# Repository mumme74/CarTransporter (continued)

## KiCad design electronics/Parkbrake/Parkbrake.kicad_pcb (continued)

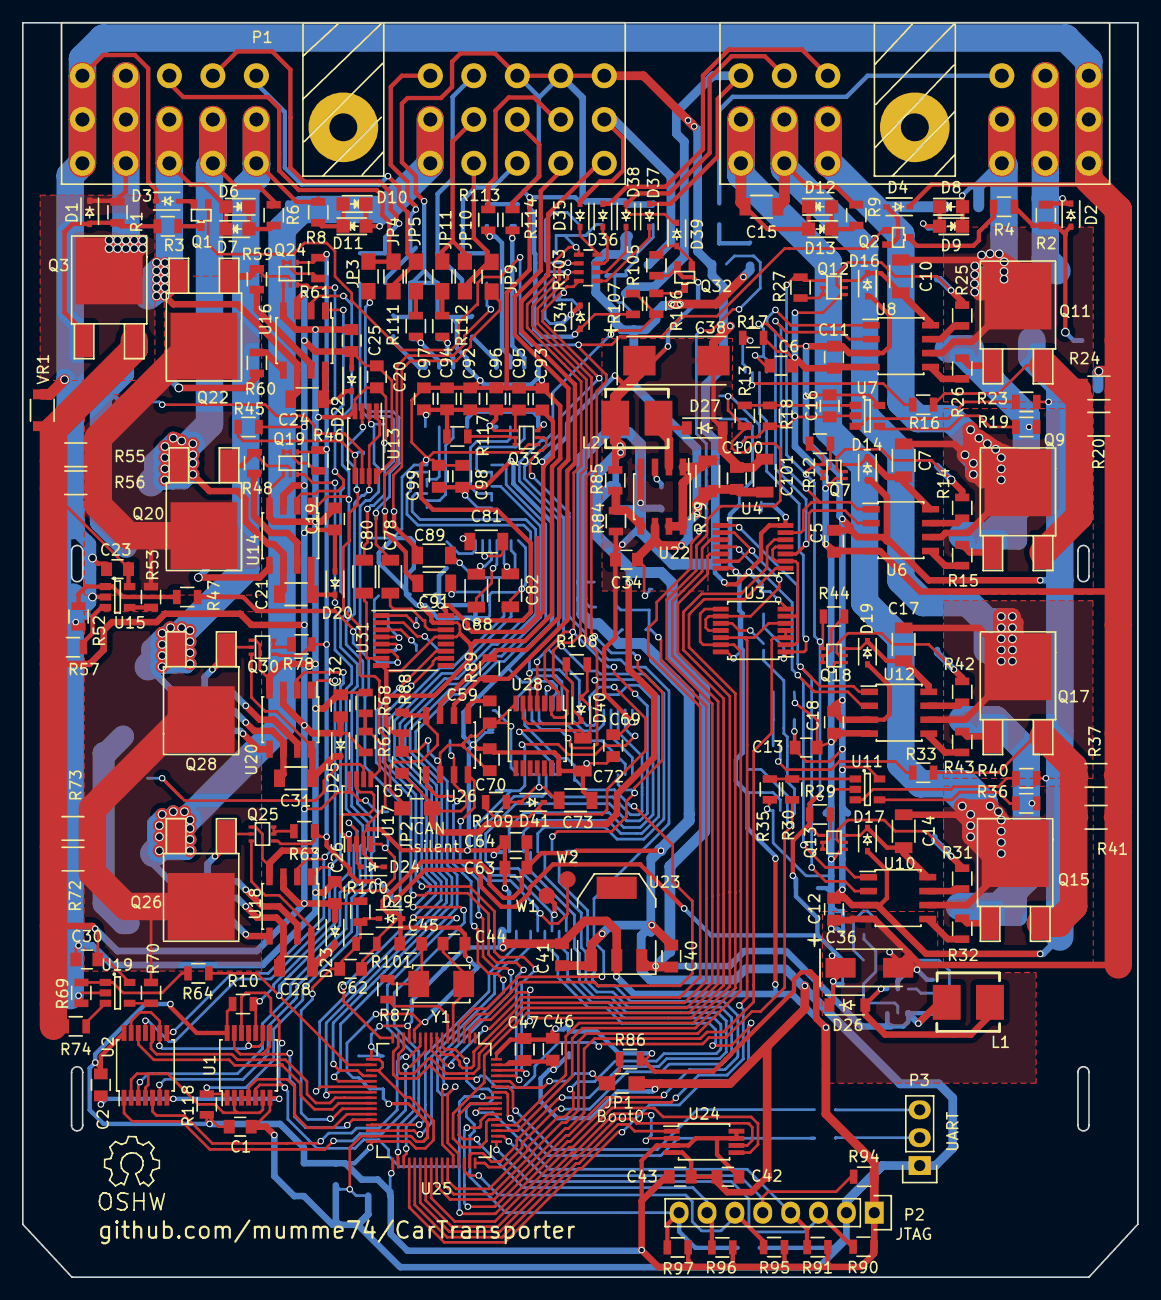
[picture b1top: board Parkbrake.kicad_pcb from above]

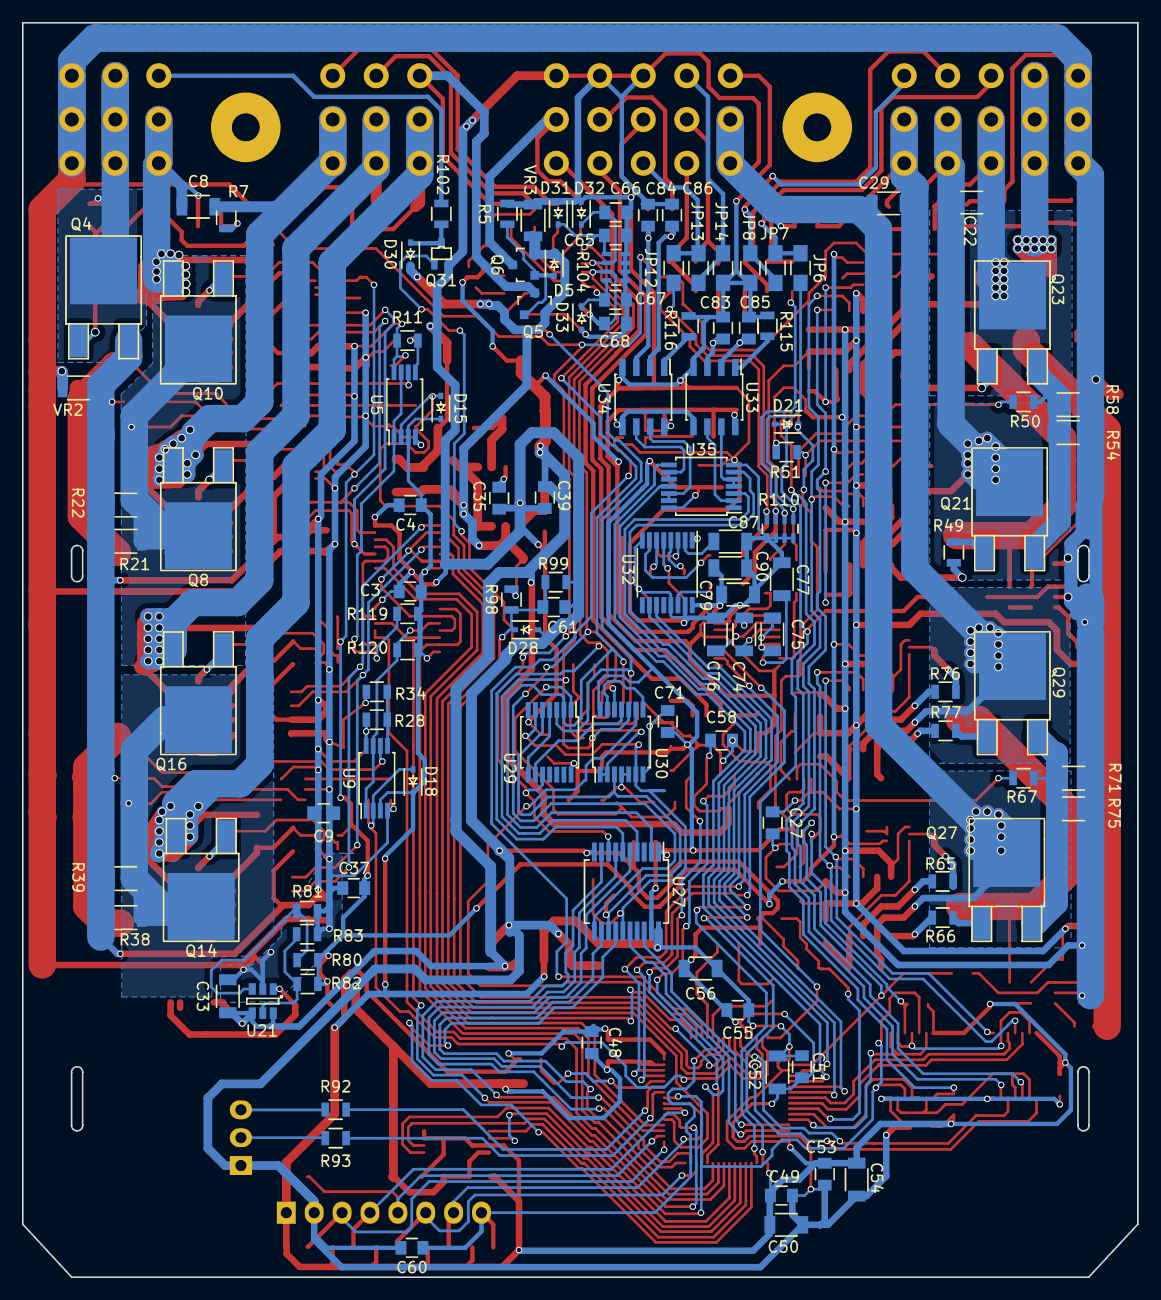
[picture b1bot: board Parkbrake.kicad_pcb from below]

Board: 2 copper layers, 101.6 x 114.3 mm, 355 parts (114 on the bottom side), 260 nets.

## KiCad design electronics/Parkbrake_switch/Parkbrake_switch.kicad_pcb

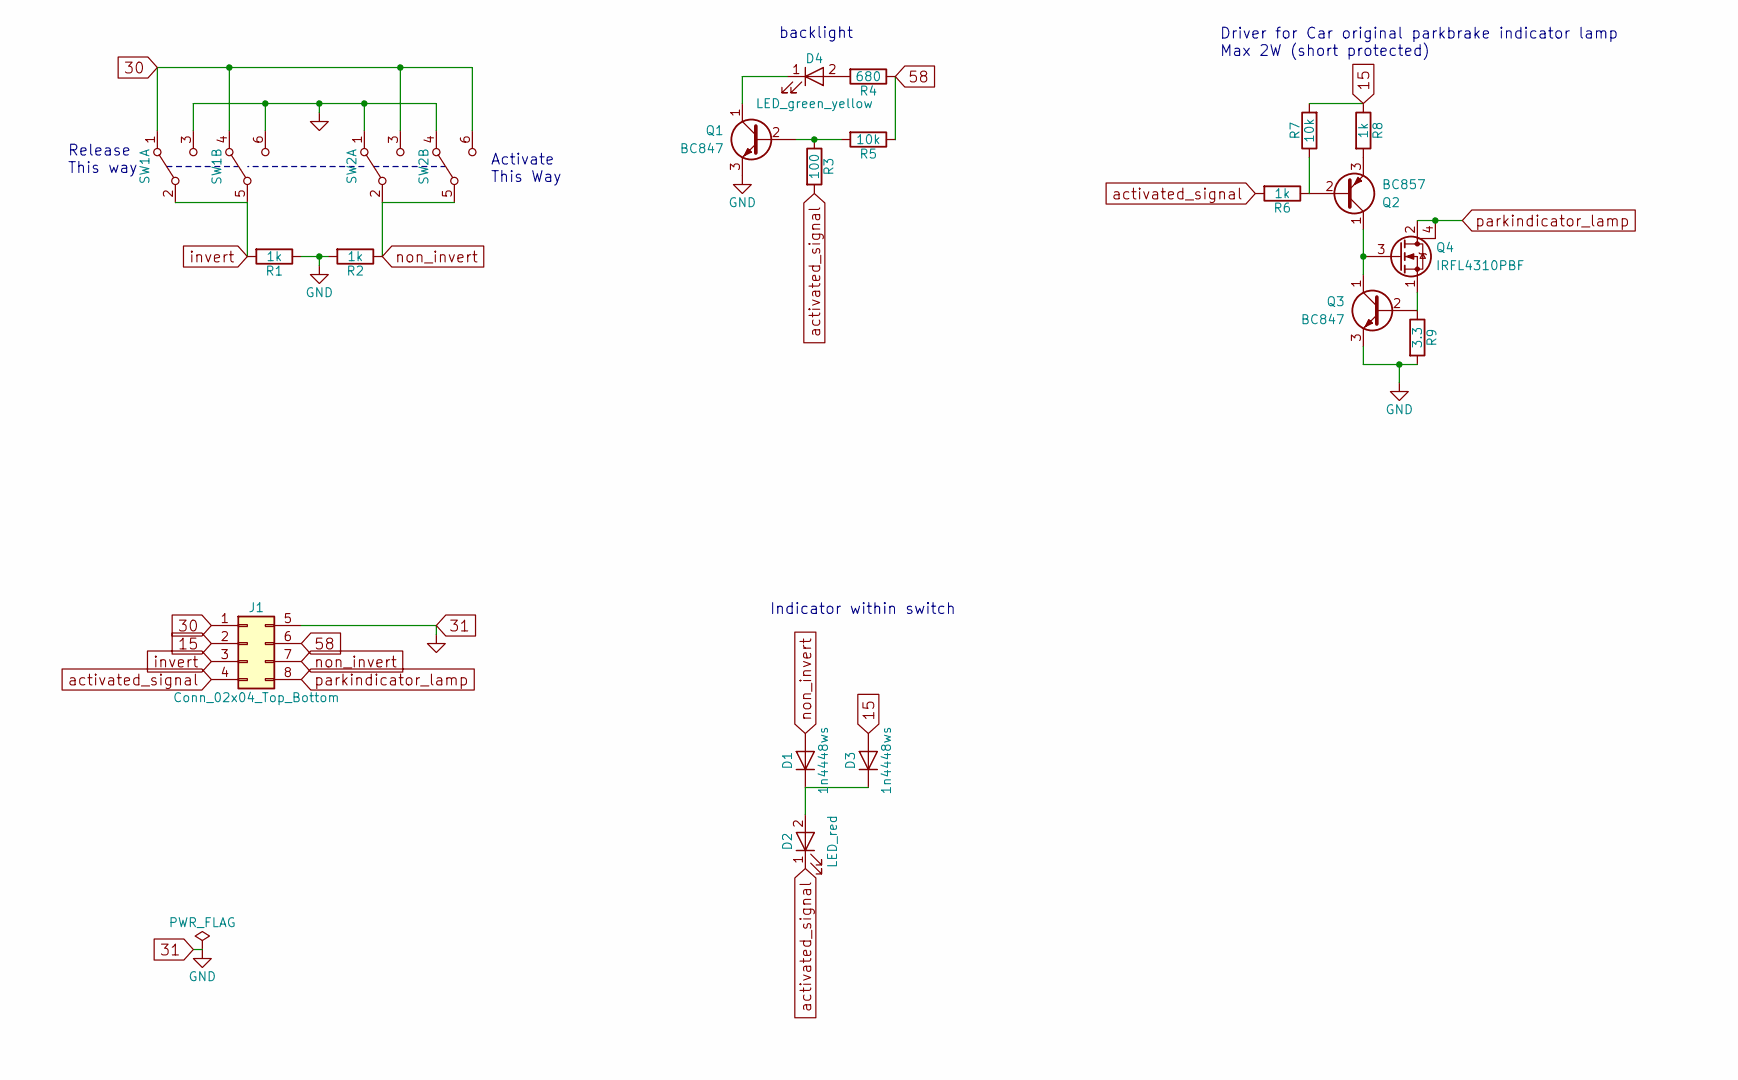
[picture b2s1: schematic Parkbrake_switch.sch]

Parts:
D1, D3: 1n4448ws; SOD-323; farnell 2453724
D2: LED_red; LED_0603; farnell 2687488
D4: LED_green_yellow; LED_0603; farnell 2762558
J1: Conn_02x04_Top_Bottom; Pin_Header_Straight_2x04_Pitch2.54mm; farnell 2356133
Q1, Q3: BC847; SOT-23; farnell 1574344
Q2: BC857; SOT-23; farnell 1773640
Q4: IRFL4310PBF; SOT-223; farnell 2101414
R1, R2, R6, R8: 1k; R_0805; farnell 2447587
R3: 100; R_0805; farnell 2694094
R4: 680; R_0805; farnell 1653028
R5, R7: 10k; R_0805; farnell 2446870
R9: 3.3; R_0805; farnell 2447656
SW1, SW2: SW_DPDT_x2; SPPH410100; farnell 1435768

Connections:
15: D3.2 (A), J1.2, R7.2, R8.1
30: J1.1, SW1.1 (A), SW1.4 (A), SW2.3 (C), SW2.6 (C)
31: J1.5, Q1.3 (E), Q3.3 (E), R1.1, R2.2, R9.2, SW1.3 (C), SW1.6 (C), SW2.1 (A), SW2.4 (A)
58: J1.6, R4.1, R5.1
unnamed: D1.1 (K), D2.2 (A), D3.1 (K)
unnamed: D4.1 (K), Q1.1 (C)
unnamed: D4.2 (A), R4.2
unnamed: Q1.2 (B), R3.1, R5.2
unnamed: Q2.1 (C), Q3.1 (C), Q4.3 (G)
unnamed: Q2.2 (B), R6.1, R7.1
unnamed: Q2.3 (E), R8.2
unnamed: Q3.2 (B), Q4.1 (S), R9.1
activated_signal: D2.1 (K), J1.4, R3.2, R6.2
invert: J1.3, R1.2, SW1.2 (B), SW1.5 (B)
non_invert: D1.2 (A), J1.7, R2.1, SW2.2 (B), SW2.5 (B)
parkindicator_lamp: J1.8, Q4.2 (D), Q4.4 (D)

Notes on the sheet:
backlight
Driver for Car original parkbrake indicator lamp Max 2W (short protected)
Indicator within switch
Release This way
Activate This Way

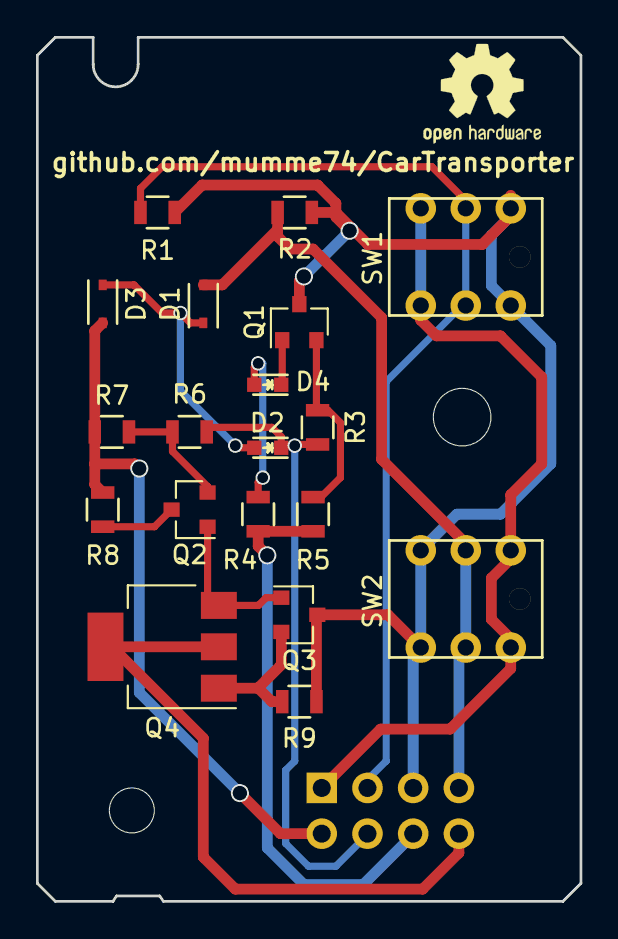
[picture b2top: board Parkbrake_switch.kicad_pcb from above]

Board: 2 copper layers, 30.2 x 48.0 mm, 20 parts (1 on the bottom side), 16 nets.

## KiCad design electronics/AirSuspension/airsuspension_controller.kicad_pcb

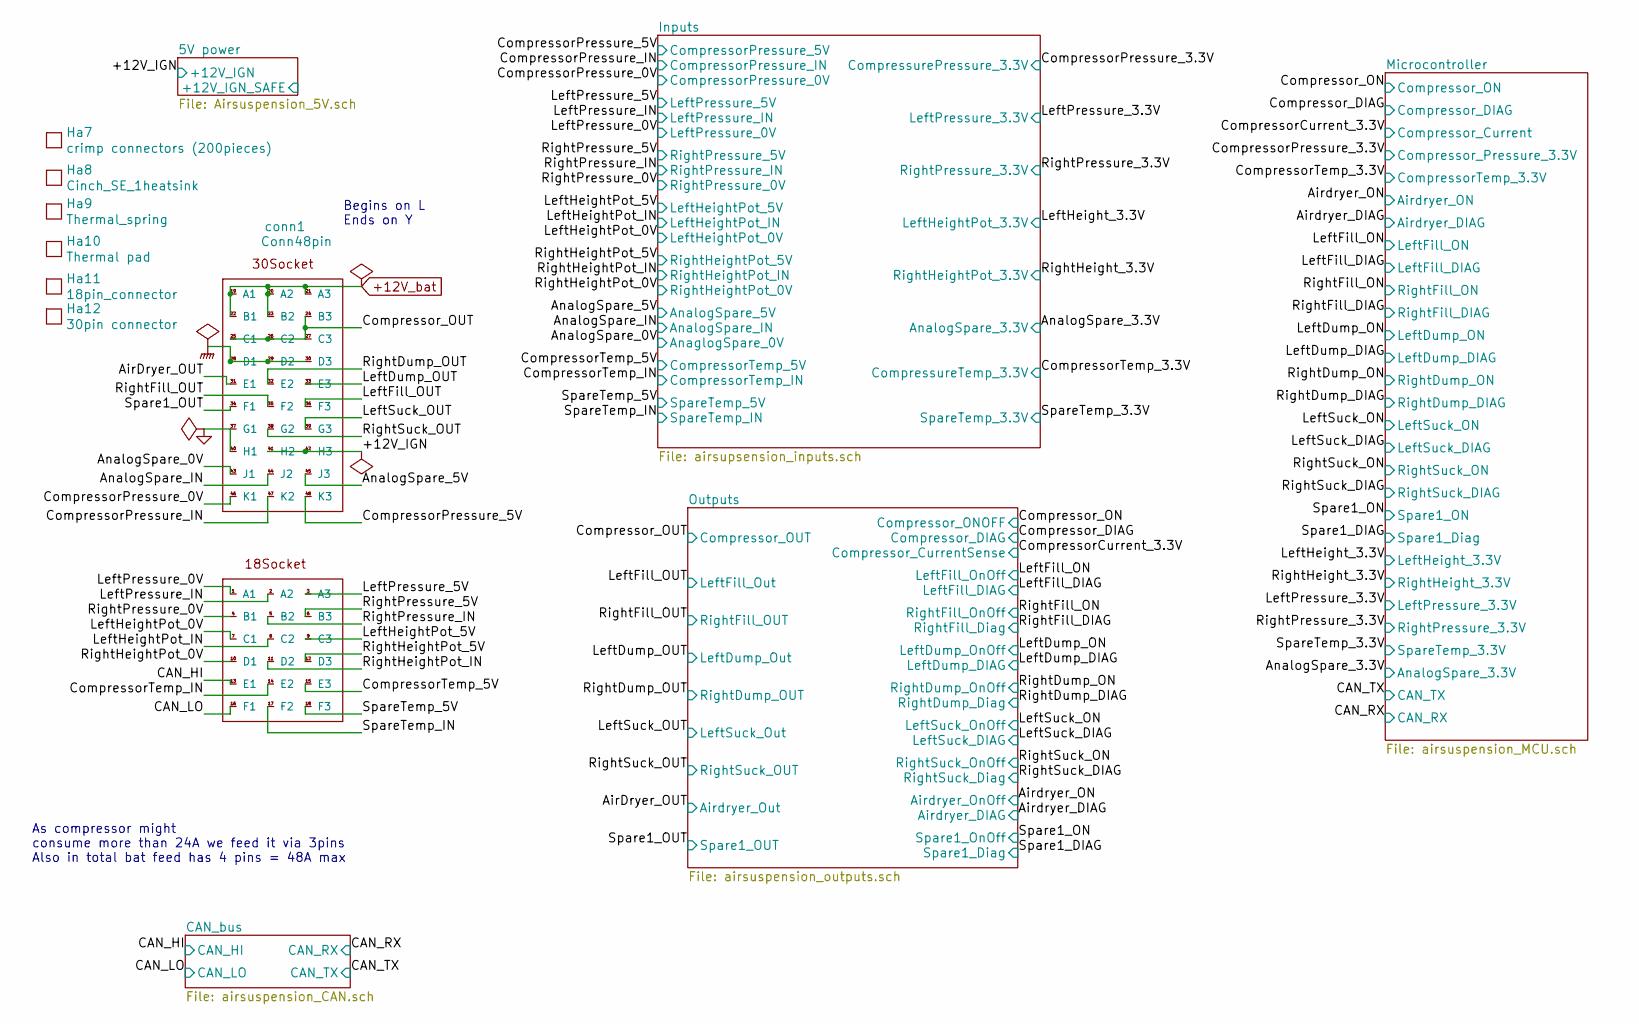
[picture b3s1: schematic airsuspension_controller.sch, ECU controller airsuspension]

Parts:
Ha7: crimp connectors (200pieces); part 4250000873; farnell 1282210
Ha8: Cinch_SE_1heatsink; part 5810130042; farnell 1282197
Ha9: Thermal_spring; part 5810000021; farnell 1282203
Ha10: Thermal pad; part FCTS73-05N; farnell 2289473
Ha11: 18pin_connector; part 5810118023; farnell 1282205
Ha12: 30pin connector; part 5810130028; farnell 1282206
conn1: Conn48pin; part 5810148007; farnell 1282184

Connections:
+12V_bat: conn1.19 (A1), conn1.20 (A2), conn1.21 (A3), conn1.22 (B1), conn1.23 (B2); also elsewhere on the board
/+12V_IGN: conn1.41 (H2), conn1.42 (H3); also elsewhere on the board
/AirDryer_OUT: conn1.31 (E1); also elsewhere on the board
/AnalogSpare_5V: conn1.45 (J3); also elsewhere on the board
/AnalogSpare_IN: conn1.44 (J2); also elsewhere on the board
/CAN_HI: conn1.13 (E1); also elsewhere on the board
/CAN_LO: conn1.16 (F1); also elsewhere on the board
/CompressorPressure_5V: conn1.48 (K3); also elsewhere on the board
/CompressorPressure_IN: conn1.47 (K2); also elsewhere on the board
/CompressorTemp_5V: conn1.15 (E3); also elsewhere on the board
/CompressorTemp_IN: conn1.14 (E2); also elsewhere on the board
/Compressor_OUT: conn1.24 (B3), conn1.25 (C1), conn1.26 (C2), conn1.27 (C3); also elsewhere on the board
/LeftDump_OUT: conn1.33 (E3); also elsewhere on the board
/LeftFill_OUT: conn1.36 (F3); also elsewhere on the board
/LeftHeightPot_5V: conn1.9 (C3); also elsewhere on the board
/LeftHeightPot_IN: conn1.8 (C2); also elsewhere on the board
/LeftPressure_5V: conn1.3 (A3); also elsewhere on the board
/LeftPressure_IN: conn1.2 (A2); also elsewhere on the board
/LeftSuck_OUT: conn1.39 (G3); also elsewhere on the board
/RightDump_OUT: conn1.32 (E2); also elsewhere on the board
/RightFill_OUT: conn1.35 (F2); also elsewhere on the board
/RightHeightPot_5V: conn1.12 (D3); also elsewhere on the board
/RightHeightPot_IN: conn1.11 (D2); also elsewhere on the board
/RightPressure_5V: conn1.6 (B3); also elsewhere on the board
/RightPressure_IN: conn1.5 (B2); also elsewhere on the board
/RightSuck_OUT: conn1.38 (G2); also elsewhere on the board
/Spare1_OUT: conn1.34 (F1); also elsewhere on the board
/SpareTemp_5V: conn1.18 (F3); also elsewhere on the board
/SpareTemp_IN: conn1.17 (F2); also elsewhere on the board
GND: conn1.1 (A1), conn1.4 (B1), conn1.7 (C1), conn1.10 (D1), conn1.37 (G1), conn1.40 (H1), conn1.43 (J1), conn1.46 (K1); also elsewhere on the board
GNDPWR: conn1.28 (D1), conn1.29 (D2), conn1.30 (D3); also elsewhere on the board

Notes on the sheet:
As compressor might consume more than 24A we feed it via 3pins Also in total bat feed has 4 pins = 48A max
Begins on L Ends on Y

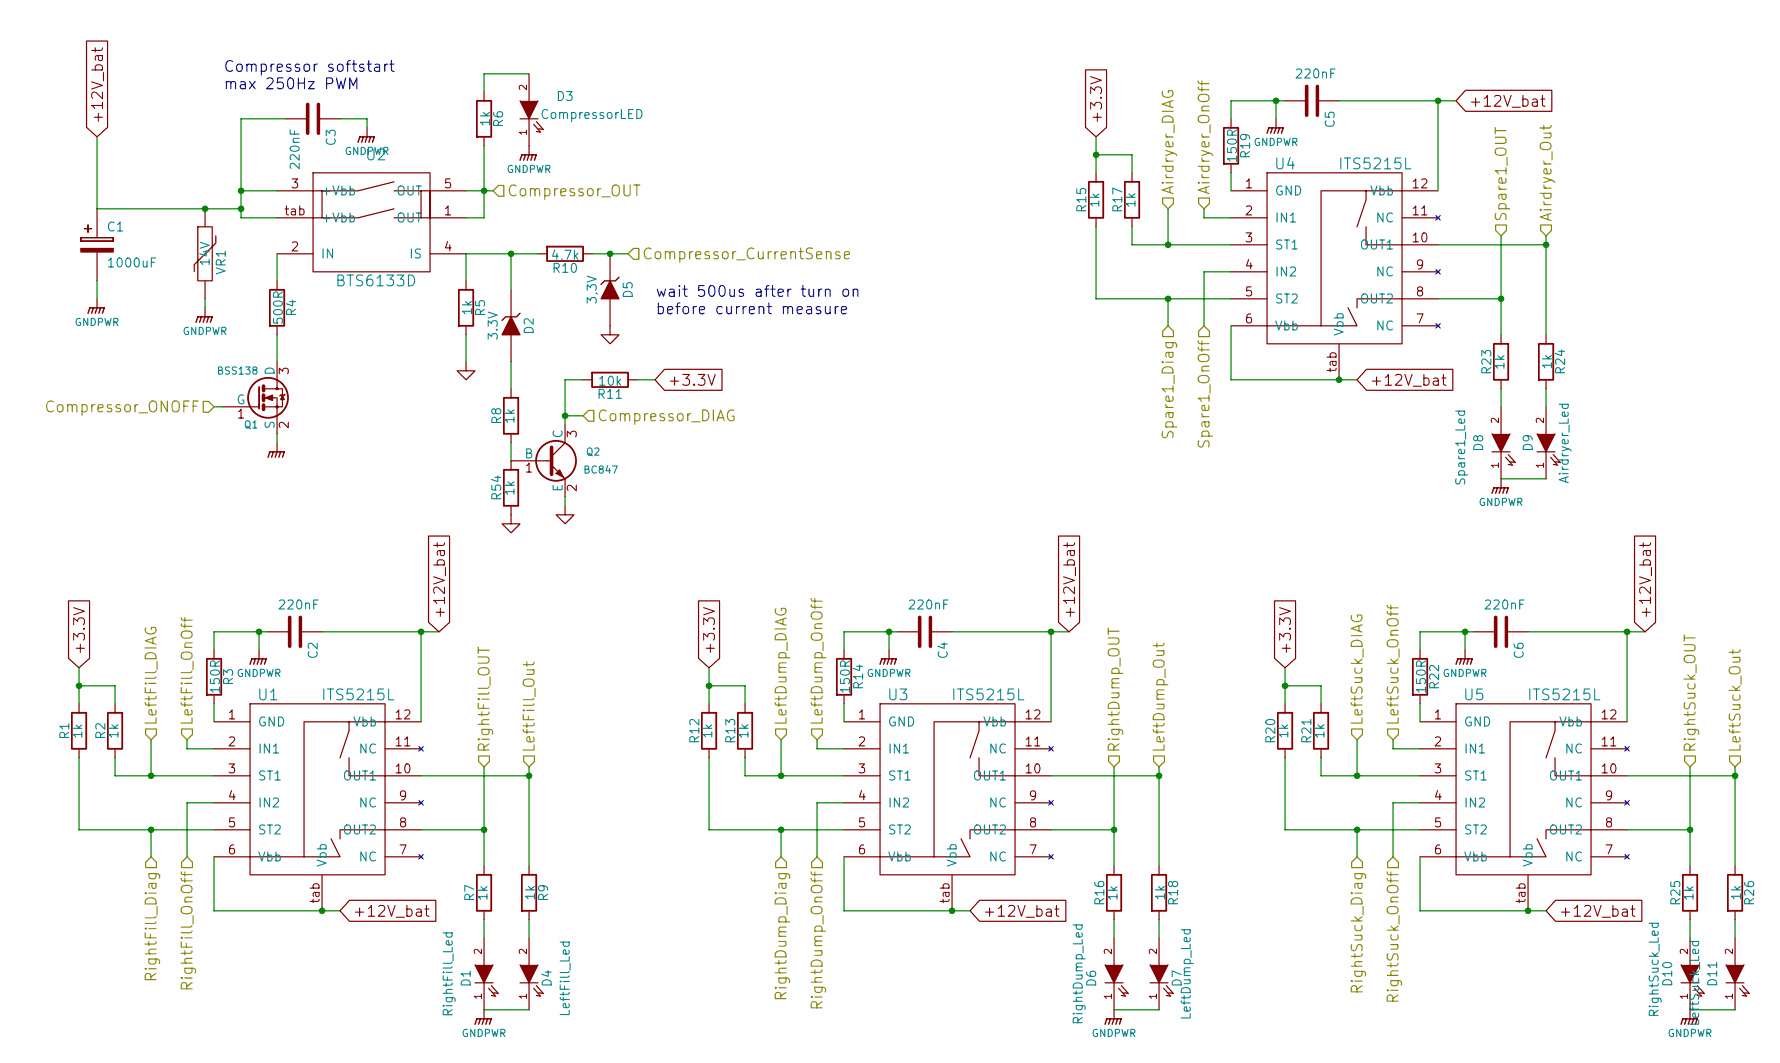
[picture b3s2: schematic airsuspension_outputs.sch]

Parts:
C1: 1000uF; SMD_Cap_16x16.5; farnell 1850136
C2, C3, C4, C5, C6: 220nF; C_0805; farnell 1288261
D1: RightFill_Led; LED_0805; farnell 2290331
D2: 3.3V; SOD-323; farnell 1757856
D3: CompressorLED; LED_0805; farnell 2290331
D4: LeftFill_Led; LED_0805; farnell 2290331
D5: 3,3V; SOD-323; farnell 1757856
D6: RightDump_Led; LED_0805; farnell 2290331
D7: LeftDump_Led; LED_0805; farnell 2290331
D8: Spare1_Led; LED_0805; farnell 2290331
D9: Airdryer_Led; LED_0805; farnell 2290331
D10: RightSuck_Led; LED_0805; farnell 2290331
D11: LeftSuck_Led; LED_0805; farnell 2290331
Q1: BSS138; SOT-23_Handsoldering; farnell 2053833
Q2: BC847; SOT-23_Handsoldering; farnell 1773609
R1, R2, R5, R7, R8, R9, R12, R13, R15, R16, R17, R18, R20, R21, R23, R24, R25, R26, R54: 1k; R_0805; farnell 1577659
R3, R14, R19, R22: 150R; R_0805; farnell 2303460
R4: 500R; R_0805; farnell 2303491
R6: 1k; R_0805
R10: 4,7k; R_0805; farnell 2333572
R11: 10k; R_0805; farnell 612522
U1, U3, U4, U5: ITS5215L; PG-DSO-12-2; farnell 1426197
U2: BTS6133D; bts6133d; farnell 1440811
VR1: 14V; R_1206_HandSoldering; farnell 1863849

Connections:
+3.3V: R1.2, R2.2, R11.1, R12.2, R13.2, R15.2, R17.2, R20.2, R21.2; also elsewhere on the board
+12V_bat: C1.1, C2.1, C3.2, C4.1, C5.1, C6.1, U1.6 (Vbb), U1.12 (Vbb), U1.tab (Vbb), U2.3 (+Vbb), U2.tab (+Vbb), U3.6 (Vbb), U3.12 (Vbb), U3.tab (Vbb), U4.6 (Vbb), U4.12 (Vbb), U4.tab (Vbb), U5.6 (Vbb), U5.12 (Vbb), U5.tab (Vbb), VR1.1; also elsewhere on the board
/AirDryer_OUT: R24.1, U4.10 (OUT1); also elsewhere on the board
/Airdryer_DIAG: R17.1, U4.3 (ST1); also elsewhere on the board
/Airdryer_ON: U4.2 (IN1); also elsewhere on the board
/CompressorCurrent_3.3V: D5.1 (K), R10.1; also elsewhere on the board
/Compressor_DIAG: Q2.3 (C), R11.2; also elsewhere on the board
/Compressor_ON: Q1.1 (G); also elsewhere on the board
/Compressor_OUT: R6.2, U2.1 (OUT), U2.5 (OUT); also elsewhere on the board
/LeftDump_DIAG: R13.1, U3.3 (ST1); also elsewhere on the board
/LeftDump_ON: U3.2 (IN1); also elsewhere on the board
/LeftDump_OUT: R18.1, U3.10 (OUT1); also elsewhere on the board
/LeftFill_DIAG: R2.1, U1.3 (ST1); also elsewhere on the board
/LeftFill_ON: U1.2 (IN1); also elsewhere on the board
/LeftFill_OUT: R9.1, U1.10 (OUT1); also elsewhere on the board
/LeftSuck_DIAG: R21.1, U5.3 (ST1); also elsewhere on the board
/LeftSuck_ON: U5.2 (IN1); also elsewhere on the board
/LeftSuck_OUT: R26.1, U5.10 (OUT1); also elsewhere on the board
/RightDump_DIAG: R12.1, U3.5 (ST2); also elsewhere on the board
/RightDump_ON: U3.4 (IN2); also elsewhere on the board
/RightDump_OUT: R16.2, U3.8 (OUT2); also elsewhere on the board
/RightFill_DIAG: R1.1, U1.5 (ST2); also elsewhere on the board
/RightFill_ON: U1.4 (IN2); also elsewhere on the board
/RightFill_OUT: R7.2, U1.8 (OUT2); also elsewhere on the board
/RightSuck_DIAG: R20.1, U5.5 (ST2); also elsewhere on the board
/RightSuck_ON: U5.4 (IN2); also elsewhere on the board
/RightSuck_OUT: R25.2, U5.8 (OUT2); also elsewhere on the board
/Spare1_DIAG: R15.1, U4.5 (ST2); also elsewhere on the board
/Spare1_ON: U4.4 (IN2); also elsewhere on the board
/Spare1_OUT: R23.2, U4.8 (OUT2); also elsewhere on the board
GND: D5.2 (A), Q2.2 (E), R5.2, R54.1; also elsewhere on the board
GNDPWR: C1.2, C2.2, C3.1, C4.2, C5.2, C6.2, D1.1 (K), D3.1 (K), D4.1 (K), D6.1 (K), D7.1 (K), D8.1 (K), D9.1 (K), D10.1 (K), D11.1 (K), Q1.2 (S), R3.1, R14.1, R19.1, R22.1, VR1.2; also elsewhere on the board
unnamed: D1.2 (A), R7.1
unnamed: D2.1 (K), R5.1, R10.2, U2.4 (IS)
unnamed: D2.2 (A), R8.2
unnamed: D3.2 (A), R6.1
unnamed: D4.2 (A), R9.2
unnamed: D6.2 (A), R16.1
unnamed: D7.2 (A), R18.2
unnamed: D8.2 (A), R23.1
unnamed: D9.2 (A), R24.2
unnamed: D10.2 (A), R25.1
unnamed: D11.2 (A), R26.2
unnamed: Q1.3 (D), R4.2
unnamed: Q2.1 (B), R8.1, R54.2
unnamed: R3.2, U1.1 (GND)
unnamed: R4.1, U2.2 (IN)
unnamed: R14.2, U3.1 (GND)
unnamed: R19.2, U4.1 (GND)
unnamed: R22.2, U5.1 (GND)

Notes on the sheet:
Compressor softstart max 250Hz PWM
wait 500us after turn on before current measure

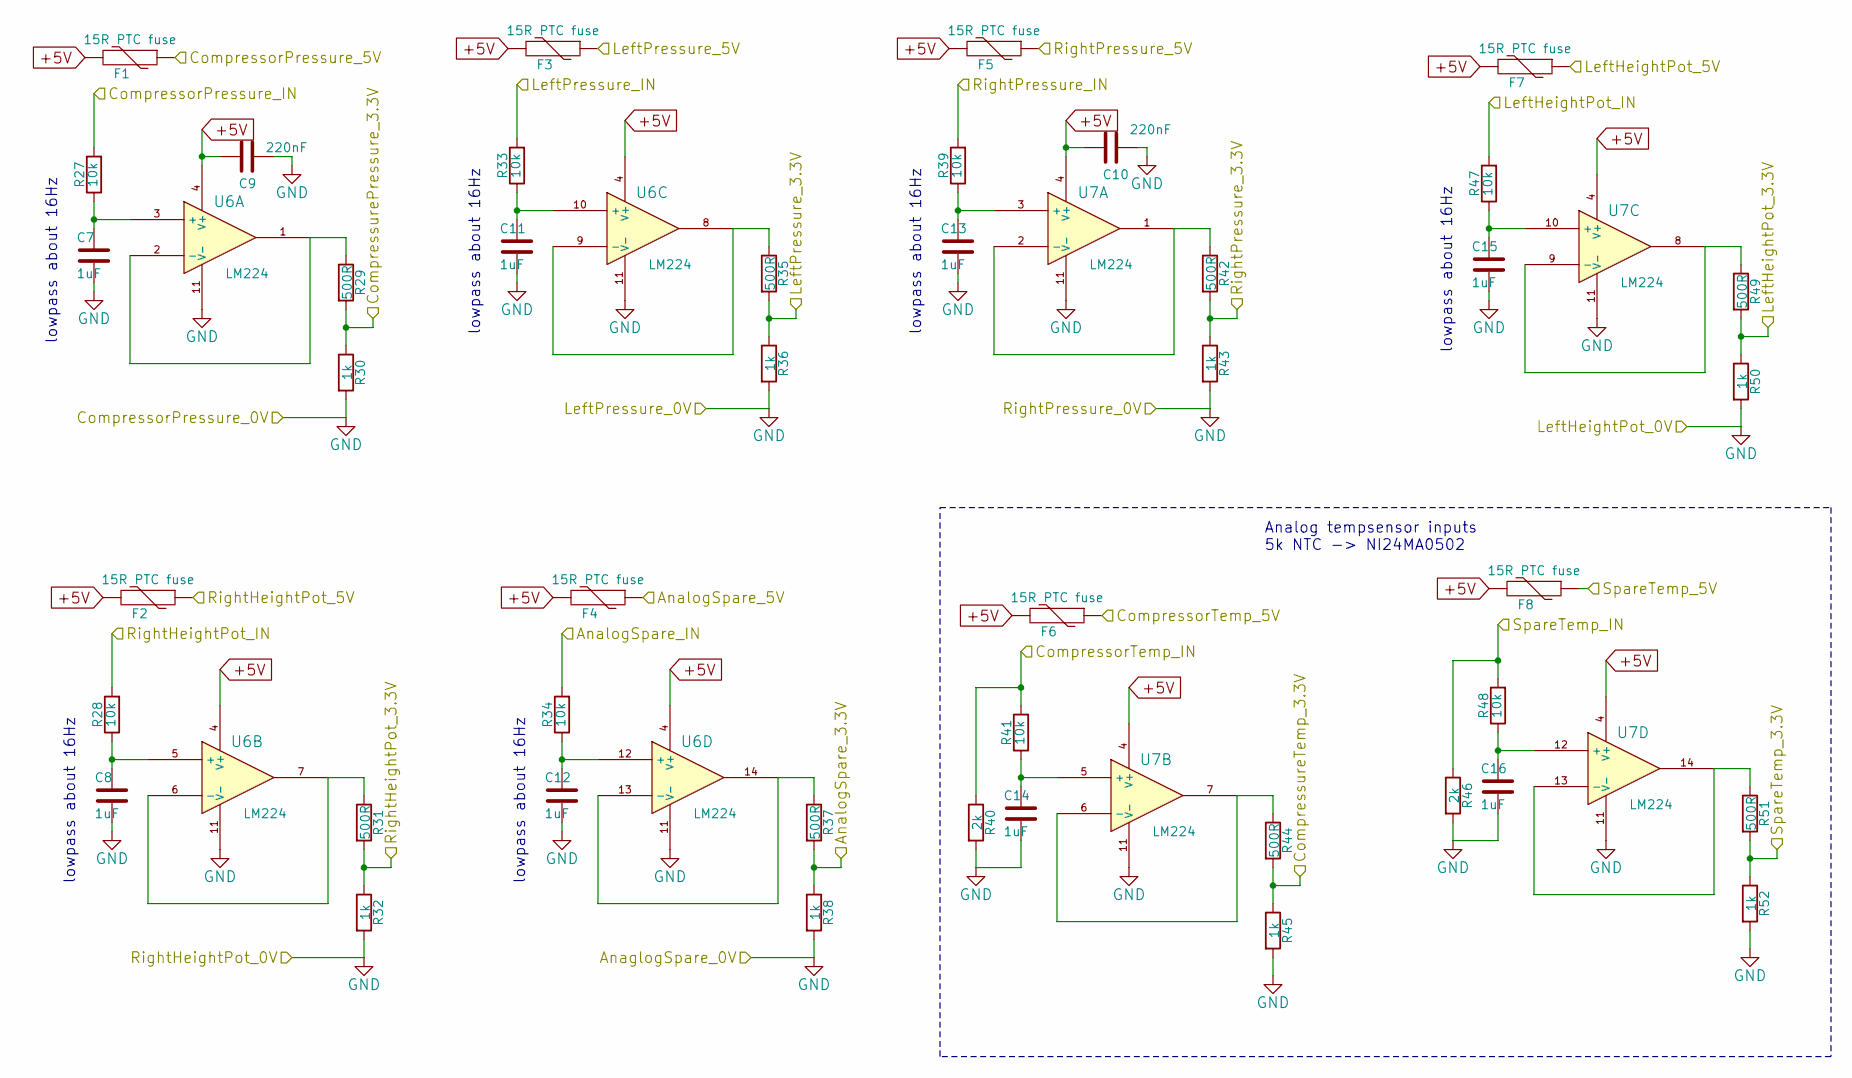
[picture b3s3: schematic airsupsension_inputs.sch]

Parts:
C7, C8, C11, C12, C13, C14, C15, C16: 1uF; C_0805; farnell 2118131
C9, C10: 220nF; C_0805; farnell 1288261
F1, F2, F3, F4, F5, F6, F7, F8: 15R PTC fuse; R_1210; farnell 1345917
R27, R28, R33, R34, R39, R41, R47, R48: 10k; R_0805; farnell 612522
R29, R31, R35, R37, R42, R44, R49, R51: 500R; R_0805; farnell 2117129
R30, R32, R36, R38, R43, R45, R50, R52: 1k; R_0805; farnell 1577659
R40, R46: 2k; R_0805; farnell 1575826
U6, U7: LM224; SOIC-14_N; farnell 1426352

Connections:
+5V: C9.2, C10.2, F1.2, F2.2, F3.2, F4.2, F5.2, F6.2, F7.2, F8.2, U6.4 (V+), U7.4 (V+); also elsewhere on the board
/AnalogSpare_3.3V: R37.2, R38.1; also elsewhere on the board
/AnalogSpare_5V: F4.1; also elsewhere on the board
/AnalogSpare_IN: R34.2; also elsewhere on the board
/CompressorPressure_3.3V: R29.2, R30.1; also elsewhere on the board
/CompressorPressure_5V: F1.1; also elsewhere on the board
/CompressorPressure_IN: R27.2; also elsewhere on the board
/CompressorTemp_3.3V: R44.2, R45.1; also elsewhere on the board
/CompressorTemp_5V: F6.1; also elsewhere on the board
/CompressorTemp_IN: R40.1, R41.2; also elsewhere on the board
/LeftHeightPot_5V: F7.1; also elsewhere on the board
/LeftHeightPot_IN: R47.2; also elsewhere on the board
/LeftHeight_3.3V: R49.2, R50.1; also elsewhere on the board
/LeftPressure_3.3V: R35.2, R36.1; also elsewhere on the board
/LeftPressure_5V: F3.1; also elsewhere on the board
/LeftPressure_IN: R33.2; also elsewhere on the board
/RightHeightPot_5V: F2.1; also elsewhere on the board
/RightHeightPot_IN: R28.2; also elsewhere on the board
/RightHeight_3.3V: R31.2, R32.1; also elsewhere on the board
/RightPressure_3.3V: R42.2, R43.1; also elsewhere on the board
/RightPressure_5V: F5.1; also elsewhere on the board
/RightPressure_IN: R39.2; also elsewhere on the board
/SpareTemp_3.3V: R51.2, R52.1; also elsewhere on the board
/SpareTemp_5V: F8.1; also elsewhere on the board
/SpareTemp_IN: R46.1, R48.2; also elsewhere on the board
GND: C7.2, C8.2, C9.1, C10.1, C11.2, C12.2, C13.2, C14.2, C15.2, C16.2, R30.2, R32.2, R36.2, R38.2, R40.2, R43.2, R45.2, R46.2, R50.2, R52.2, U6.11 (V-), U7.11 (V-); also elsewhere on the board
unnamed: C7.1, R27.1, U6.3 (+)
unnamed: C8.1, R28.1, U6.5 (+)
unnamed: C11.1, R33.1, U6.10 (+)
unnamed: C12.1, R34.1, U6.12 (+)
unnamed: C13.1, R39.1, U7.3 (+)
unnamed: C14.1, R41.1, U7.5 (+)
unnamed: C15.1, R47.1, U7.10 (+)
unnamed: C16.1, R48.1, U7.12 (+)
unnamed: R29.1, U6.1, U6.2 (-)
unnamed: R31.1, U6.6 (-), U6.7
unnamed: R35.1, U6.8, U6.9 (-)
unnamed: R37.1, U6.13 (-), U6.14
unnamed: R42.1, U7.1, U7.2 (-)
unnamed: R44.1, U7.6 (-), U7.7
unnamed: R49.1, U7.8, U7.9 (-)
unnamed: R51.1, U7.13 (-), U7.14

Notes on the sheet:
lowpass about 16Hz
Analog tempsensor inputs 5k NTC -> NI24MA0502

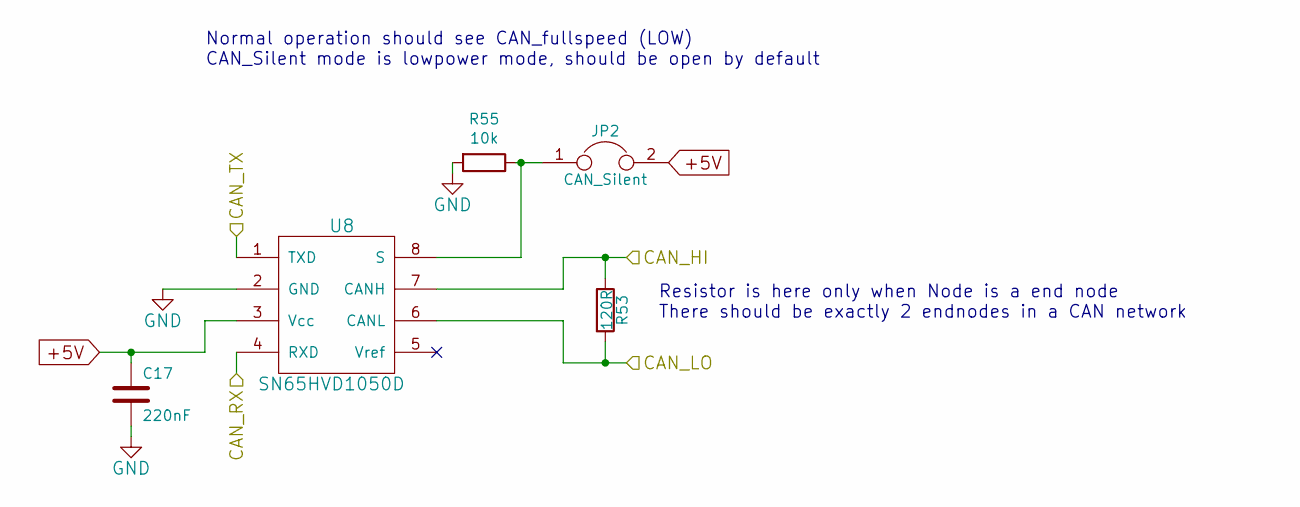
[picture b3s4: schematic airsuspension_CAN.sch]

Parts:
C17: 220nF; C_0805; farnell 1288261
JP2: CAN_Silent; NetTie-I_SMD
R53: 120R; R_0805_HandSoldering; farnell 2303452
R55: 10k; R_0805_HandSoldering; farnell 9332391
U8: SN65HVD1050D; SOIC-8_3.9x4.9mm_Pitch1.27mm; farnell 1220984

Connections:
+5V: C17.1, JP2.2, U8.3 (Vcc); also elsewhere on the board
/CAN_HI: R53.1, U8.7 (CANH); also elsewhere on the board
/CAN_LO: R53.2, U8.6 (CANL); also elsewhere on the board
/CAN_RX: U8.4 (RXD); also elsewhere on the board
/CAN_TX: U8.1 (TXD); also elsewhere on the board
GND: C17.2, R55.2, U8.2 (GND); also elsewhere on the board
unnamed: JP2.1, R55.1, U8.8 (S)

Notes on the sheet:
Normal operation should see CAN_fullspeed (LOW) CAN_Silent mode is lowpower mode, should be open by default
Resistor is here only when Node is a end node There should be exactly 2 endnodes in a CAN network

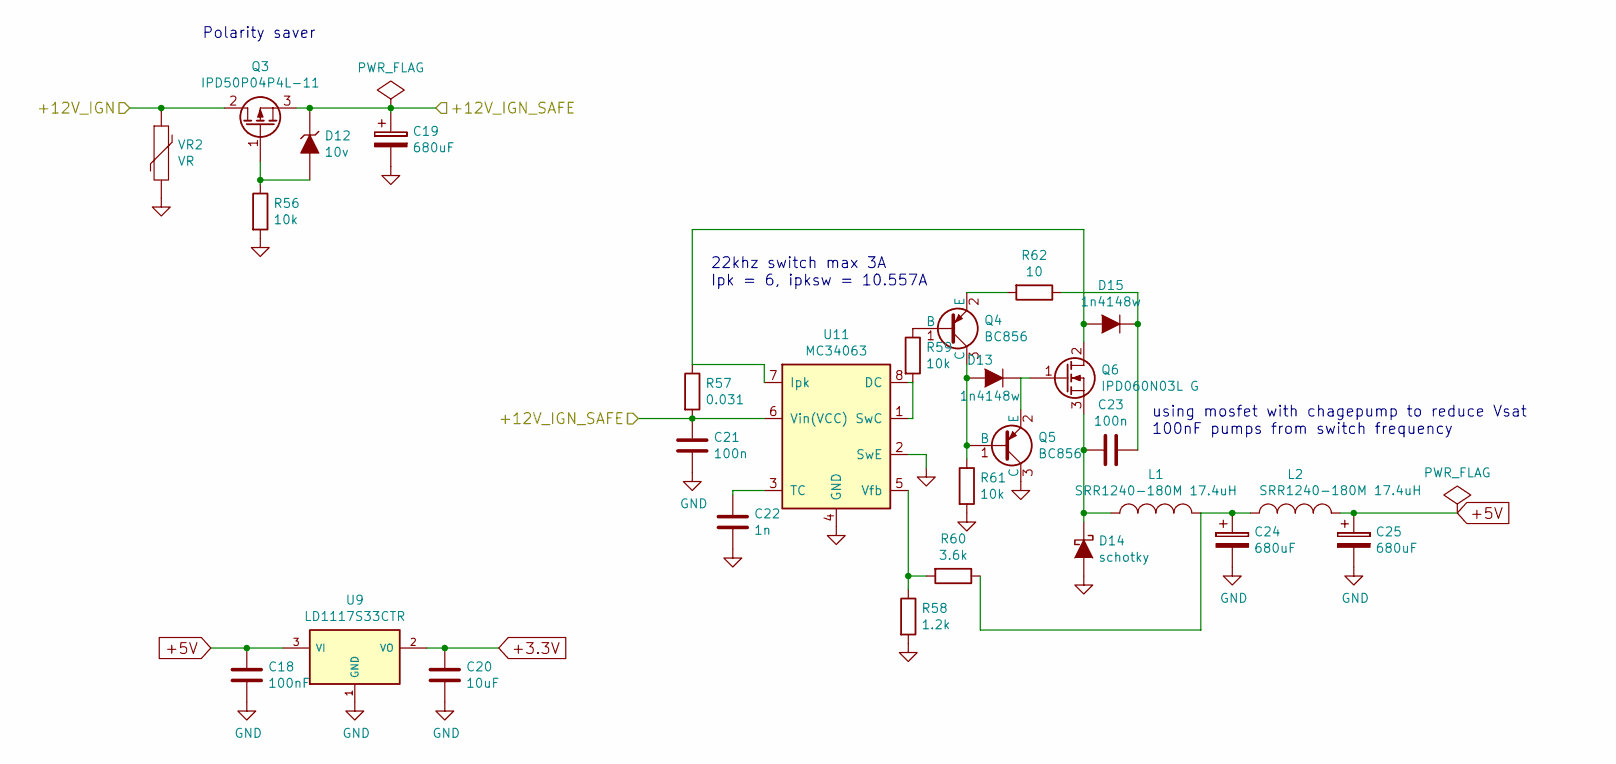
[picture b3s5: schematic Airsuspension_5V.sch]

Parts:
C18: 100nF; C_0805_HandSoldering; farnell 2496940
C19, C24, C25: 680uF; c_elec_10x10.5; part EEEHAC681UAP; farnell 2326228
C20: 10uF; C_1206_HandSoldering; farnell 1463368
C21, C23: 100n; C_0805_HandSoldering; part 0805B104J500CT; farnell 2496940
C22: 1n; C_0805_HandSoldering; part 0805B102J500CT; farnell 2496932
D12: 10v; SOD-323; part BZT52C10S; farnell 1466026
D13, D15: 1n4148w; SOD-323; farnell 1466524
D14: schotky; DO-214AB_Handsoldering; part MBRS340T3G; farnell 9557377
L1, L2: SRR1240-180M 17.4uH; Neosid_Inductor_SM-NE127; farnell 2333725
Q3: IPD50P04P4L-11; TO-252-2Lead; part IPD50P04P4L-11; farnell 2443434
Q4, Q5: BC856; SOT-23_Handsoldering; part BC856B-7-F; farnell 1773623
Q6: IPD060N03L G; TO-252-2Lead; farnell 1775575
R56, R59, R61: 10k; R_0805_HandSoldering; farnell 9332391
R57: 0.031; R_1206_HandSoldering; part LR1206-R033FW; farnell 1099911
R58: 1.2k; R_0805_HandSoldering; farnell 9332499
R60: 3.6k; R_0805_HandSoldering; farnell 9333118
R62: 10; R_0805_HandSoldering; farnell 9332766
U9: LD1117S33CTR; SOT-223; farnell 1467779
U11: MC34063; SOIC-8_3.9x4.9mm_Pitch1.27mm; part MC34063ABD-TR; farnell 1087205
VR2: VR; R_1206_HandSoldering; part VC120618A400DP; farnell 1301938

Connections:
+3.3V: C20.1, U9.2 (VO); also elsewhere on the board
+5V: C18.1, C25.1, L2.2, U9.3 (VI); also elsewhere on the board
/5V power/+12V_IGN_SAFE: C19.1, C21.1, D12.1 (K), Q3.3 (S), R57.2, U11.6 (Vin(VCC))
/+12V_IGN: Q3.2 (D), VR2.1; also elsewhere on the board
GND: C18.2, C19.2, C20.2, C21.2, C22.2, C24.2, C25.2, D14.2 (A), Q5.3 (C), R56.2, R58.2, R61.2, U9.1 (GND), U11.2 (SwE), U11.4 (GND), VR2.2; also elsewhere on the board
unnamed: C22.1, U11.3 (TC)
unnamed: C23.1, D15.1 (K), R62.1
unnamed: C23.2, D14.1 (K), L1.1, Q6.3 (S)
unnamed: C24.1, L1.2, L2.1, R60.1
unnamed: D12.2 (A), Q3.1 (G), R56.1
unnamed: D13.1 (K), Q5.2 (E), Q6.1 (G)
unnamed: D13.2 (A), Q4.3 (C), Q5.1 (B), R61.1
unnamed: D15.2 (A), Q6.2 (D), R57.1, U11.7 (Ipk)
unnamed: Q4.1 (B), R59.1
unnamed: Q4.2 (E), R62.2
unnamed: R58.1, R60.2, U11.5 (Vfb)
unnamed: R59.2, U11.1 (SwC), U11.8 (DC)

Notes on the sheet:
22khz switch max 3A Ipk = 6, ipksw = 10.557A
using mosfet with chagepump to reduce Vsat 100nF pumps from switch frequency
Polarity saver
